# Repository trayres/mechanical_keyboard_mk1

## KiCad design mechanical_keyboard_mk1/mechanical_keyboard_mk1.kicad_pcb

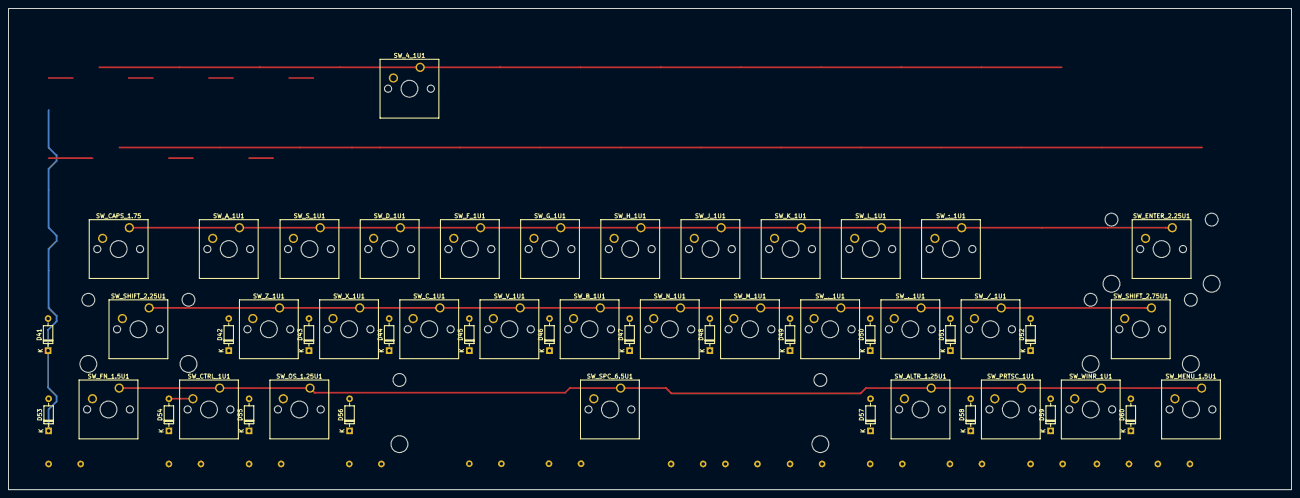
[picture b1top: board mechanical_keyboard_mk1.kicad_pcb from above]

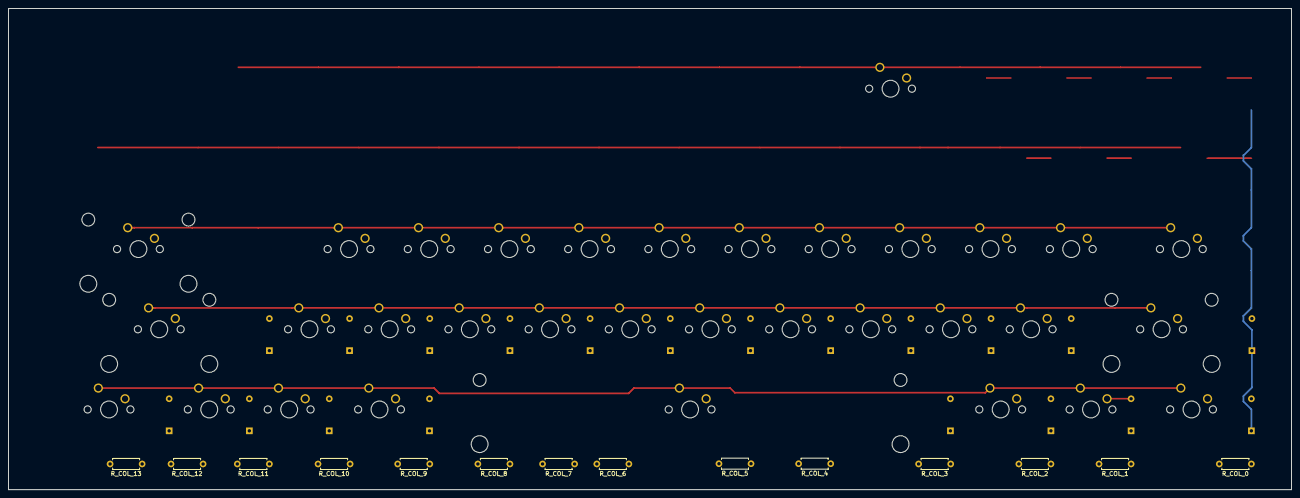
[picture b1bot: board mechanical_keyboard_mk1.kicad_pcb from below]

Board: 2 copper layers, 304.8 x 114.3 mm, 68 parts (14 on the bottom side), 37 nets.

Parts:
D41, D42, D43, D44, D45, D46, D47, D48, D49, D50, D51, D52, D53, D54, D55, D56, D57, D58, D59, D60: 1N4148; D_DO-35_SOD27_P7.62mm_Horizontal
R_COL_0, R_COL_1, R_COL_2, R_COL_3, R_COL_4, R_COL_5, R_COL_6, R_COL_7, R_COL_8, R_COL_9, R_COL_10, R_COL_11, R_COL_12, R_COL_13: 10k; R_Axial_DIN0207_L6.3mm_D2.5mm_P7.62mm_Horizontal
SW_: SW_Cherry_MX_1.00u_PCB
SW_4_1U1, SW_._1U1: SW_SPST; SW_Cherry_MX_1.00u_PCB
SW_,_1U1: SW_SPST; SW_Cherry_MX_1.00u_PCB
SW_/_1U1: SW_SPST; SW_Cherry_MX_1.00u_PCB
SW_;_1U1: SW_SPST; SW_Cherry_MX_1.00u_PCB
SW_ALTR_1.25U1: SW_SPST; SW_Cherry_MX_1.25u_PCB
SW_A_1U1: SW_SPST; SW_Cherry_MX_1.00u_PCB
SW_B_1U1: SW_SPST; SW_Cherry_MX_1.00u_PCB
SW_CAPS_1.75: SW_SPST; SW_Cherry_MX_1.75u_PCB
SW_CTRL_1U1: SW_SPST; SW_Cherry_MX_1.00u_PCB
SW_C_1U1: SW_SPST; SW_Cherry_MX_1.00u_PCB
SW_D_1U1: SW_SPST; SW_Cherry_MX_1.00u_PCB
SW_ENTER_2.25U1: SW_SPST; SW_Cherry_MX_2.25u_PCB
SW_FN_1.5U1: SW_SPST; SW_Cherry_MX_1.50u_PCB
SW_F_1U1: SW_SPST; SW_Cherry_MX_1.00u_PCB
SW_G_1U1: SW_SPST; SW_Cherry_MX_1.00u_PCB
SW_H_1U1: SW_SPST; SW_Cherry_MX_1.00u_PCB
SW_J_1U1: SW_SPST; SW_Cherry_MX_1.00u_PCB
SW_K_1U1: SW_SPST; SW_Cherry_MX_1.00u_PCB
SW_L_1U1: SW_SPST; SW_Cherry_MX_1.00u_PCB
SW_MENU_1.5U1: SW_SPST; SW_Cherry_MX_1.50u_PCB
SW_M_1U1: SW_SPST; SW_Cherry_MX_1.00u_PCB
SW_N_1U1: SW_SPST; SW_Cherry_MX_1.00u_PCB
SW_OS_1.25U1: SW_SPST; SW_Cherry_MX_1.25u_PCB
SW_PRTSC_1U1: SW_SPST; SW_Cherry_MX_1.00u_PCB
SW_SHIFT_2.25U1: SW_SPST; SW_Cherry_MX_2.25u_PCB
SW_SHIFT_2.75U1: SW_SPST; SW_Cherry_MX_2.75u_PCB
SW_SPC_6.5U1: SW_SPST; SW_Cherry_MX_6.5u_PCB
SW_S_1U1: SW_SPST; SW_Cherry_MX_1.00u_PCB
SW_V_1U1: SW_SPST; SW_Cherry_MX_1.00u_PCB
SW_WINR_1U1: SW_SPST; SW_Cherry_MX_1.00u_PCB
SW_X_1U1: SW_SPST; SW_Cherry_MX_1.00u_PCB
SW_Z_1U1: SW_SPST; SW_Cherry_MX_1.00u_PCB

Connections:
/key_matrix/COL_0: D41.1, D53.1, R_COL_0.1
/key_matrix/COL_1: D42.1, D54.1, R_COL_1.1
/key_matrix/COL_2: D43.1, D55.1, R_COL_2.1
/key_matrix/COL_3: D44.1, D56.1, R_COL_3.1
/key_matrix/COL_4: D45.1, R_COL_4.1
/key_matrix/COL_5: D46.1, R_COL_5.1
/key_matrix/COL_6: D47.1, R_COL_6.1
/key_matrix/COL_7: D48.1, R_COL_7.1
/key_matrix/COL_8: D49.1, R_COL_8.1
/key_matrix/COL_9: D50.1, D57.1, R_COL_9.1
/key_matrix/COL_10: D51.1, D58.1, R_COL_10.1
/key_matrix/COL_11: D52.1, D59.1, R_COL_11.1
/key_matrix/COL_12: D60.1, R_COL_12.1
/key_matrix/ROW_2: SW_;_1U1.1, SW_A_1U1.1, SW_CAPS_1.75.1, SW_D_1U1.1, SW_ENTER_2.25U1.1, SW_F_1U1.1, SW_G_1U1.1, SW_H_1U1.1, SW_J_1U1.1, SW_K_1U1.1, SW_L_1U1.1, SW_S_1U1.1
/key_matrix/ROW_3: SW_,_1U1.1, SW_._1U1.1, SW_/_1U1.1, SW_B_1U1.1, SW_C_1U1.1, SW_M_1U1.1, SW_N_1U1.1, SW_SHIFT_2.25U1.1, SW_SHIFT_2.75U1.1, SW_V_1U1.1, SW_X_1U1.1, SW_Z_1U1.1
/key_matrix/ROW_4: SW_ALTR_1.25U1.1, SW_CTRL_1U1.1, SW_FN_1.5U1.1, SW_MENU_1.5U1.1, SW_OS_1.25U1.1, SW_PRTSC_1U1.1, SW_SPC_6.5U1.1, SW_WINR_1U1.1
GND: R_COL_0.2, R_COL_1.2, R_COL_2.2, R_COL_3.2, R_COL_4.2, R_COL_5.2, R_COL_6.2, R_COL_7.2, R_COL_8.2, R_COL_9.2, R_COL_10.2, R_COL_11.2, R_COL_12.2, R_COL_13.2
unnamed: D41.2, SW_SHIFT_2.25U1.2
unnamed: D42.2, SW_Z_1U1.2
unnamed: D43.2, SW_X_1U1.2
unnamed: D44.2, SW_C_1U1.2
unnamed: D45.2, SW_V_1U1.2
unnamed: D46.2, SW_B_1U1.2
unnamed: D47.2, SW_N_1U1.2
unnamed: D48.2, SW_M_1U1.2
unnamed: D49.2, SW_,_1U1.2
unnamed: D50.2, SW_._1U1.2
unnamed: D51.2, SW_/_1U1.2
unnamed: D52.2, SW_SHIFT_2.75U1.2
unnamed: D53.2, SW_FN_1.5U1.2
unnamed: D54.2, SW_CTRL_1U1.2
unnamed: D55.2, SW_OS_1.25U1.2
unnamed: D56.2, SW_SPC_6.5U1.2
unnamed: D57.2, SW_ALTR_1.25U1.2
unnamed: D58.2, SW_PRTSC_1U1.2
unnamed: D59.2, SW_WINR_1U1.2
unnamed: D60.2, SW_MENU_1.5U1.2

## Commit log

2019-06-03 Initial commit - first row
